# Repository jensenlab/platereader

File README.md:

<p align="center">
  <b>Instantaneous Spectrophotometer for 96 Well Plate</b><br><br>
  Adam Dama<br>
  Jensen Lab<br>
  University of Illinois at Urbana-Champaign<br>
  Department of Bioengineering and Carl R. Woese Institute for Genomic Biology<br>
  <br>
</p>

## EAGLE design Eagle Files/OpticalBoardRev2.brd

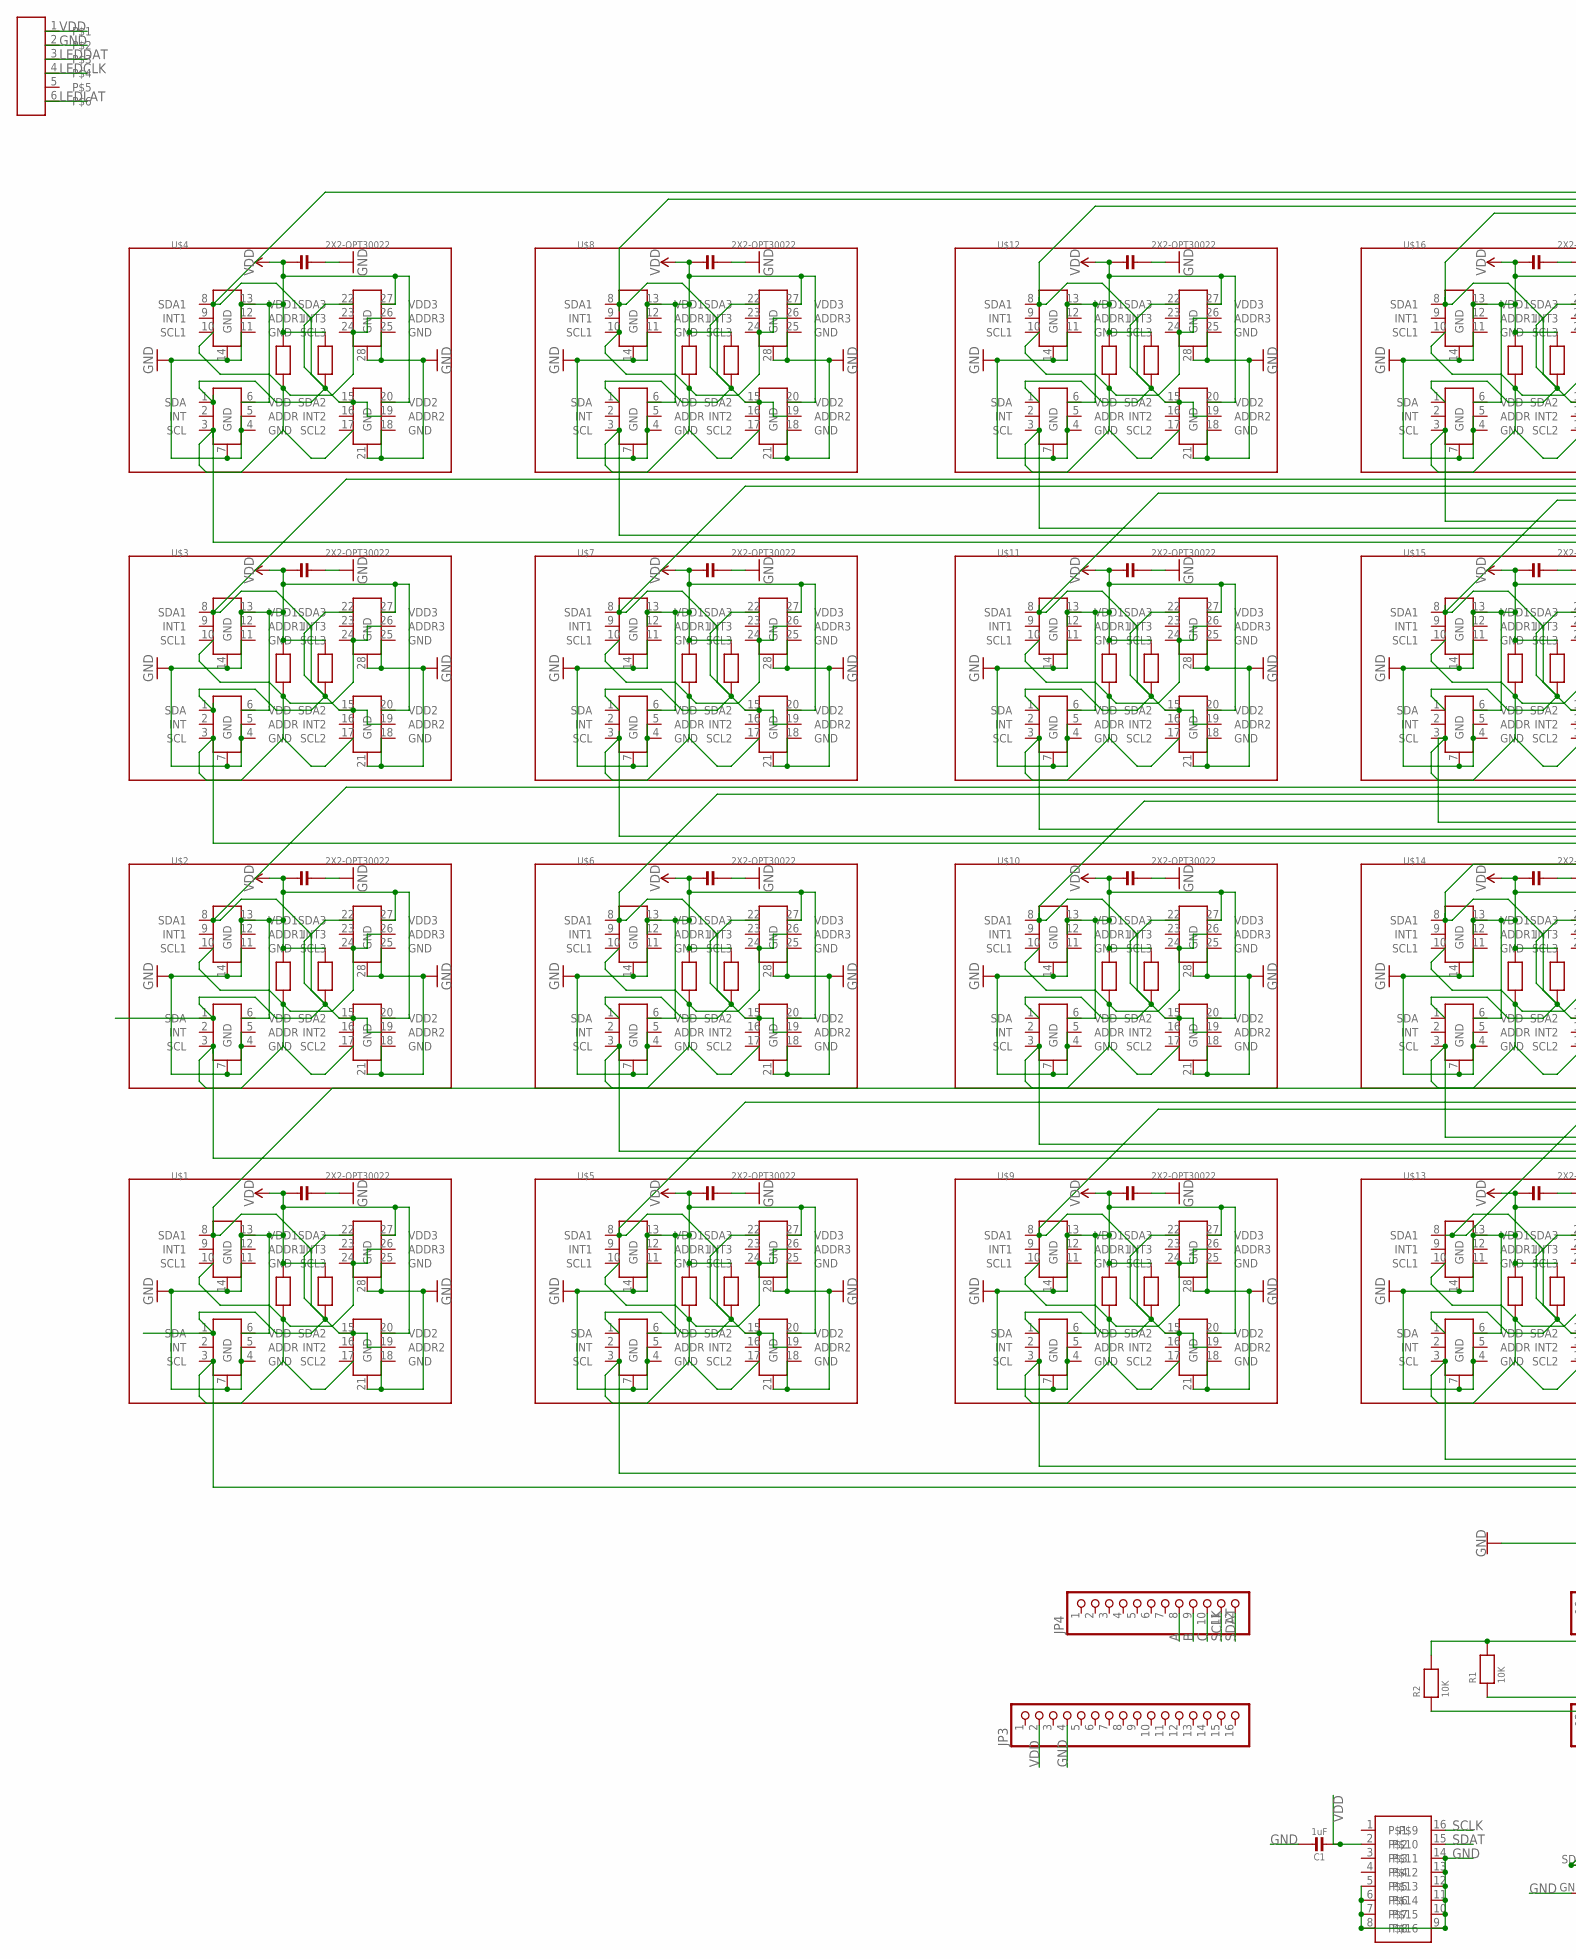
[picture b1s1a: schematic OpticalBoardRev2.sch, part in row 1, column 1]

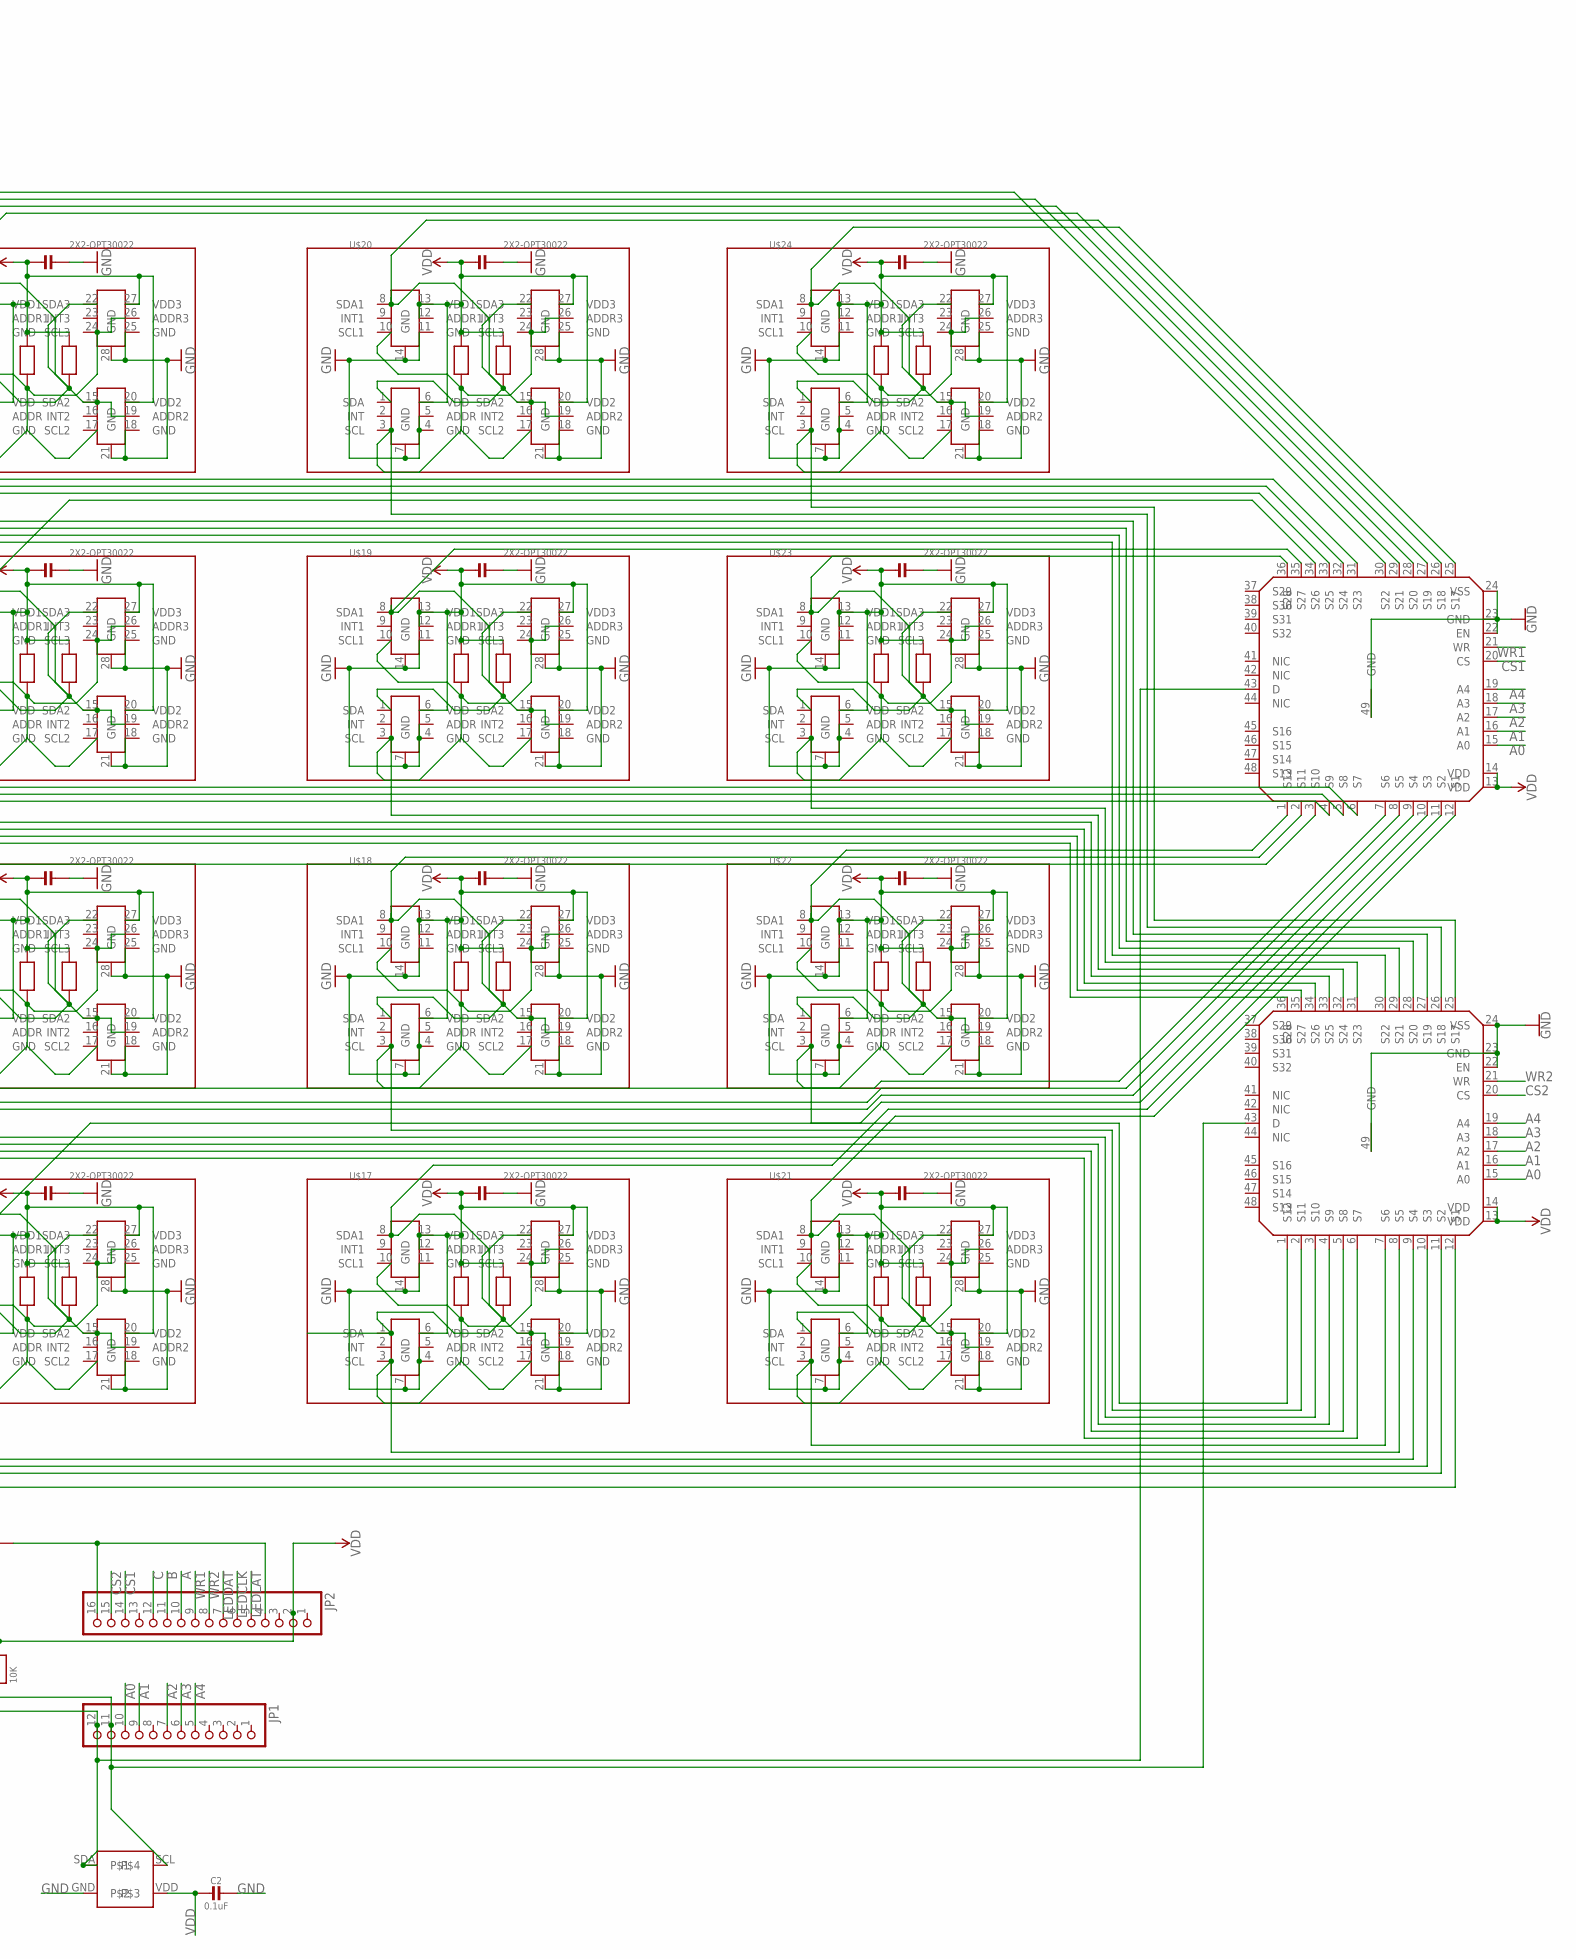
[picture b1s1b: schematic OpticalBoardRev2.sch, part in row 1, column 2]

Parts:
C1: 1uF; _0805
C2: 0.1uF; _0805
JP1, JP4: HEADER-1X12; 1X12_ROUND
JP2, JP3: HEADER-1X16ROUND; 1X16_ROUND
R1, R2: 10K; _0805
U$1, U$2, U$3, U$4, U$5, U$6, U$7, U$8, U$9, U$10, U$11, U$12, U$13, U$14, U$15, U$16, U$17, U$18, U$19, U$20, U$21, U$22, U$23, U$24: 2X2-OPT30022; 2X2-OPT3002-2
U$25: CONNECTOR_6PIN
U$26: 32MUXTOP; 32MUX
U$27: 32MUXBOT; 32MUX_BOT
U$28: RTC
U$29: TH_NEW

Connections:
A: JP2.10, JP4.8
A0: JP1.10, U$26.15 (A0), U$27.15 (A0)
A1: JP1.9, U$26.16 (A1), U$27.16 (A1)
A2: JP1.7, U$26.17 (A2), U$27.17 (A2)
A3: JP1.6, U$26.18 (A3), U$27.18 (A3)
A4: JP1.5, U$26.19 (A4), U$27.19 (A4)
B: JP2.11, JP4.9
C: JP2.12, JP4.10
CS1: JP2.14, U$26.20 (CS)
CS2: JP2.15, U$27.20 (CS)
GND: C1.1, C2.1, JP2.4, JP2.16, JP3.4, U$1.4 (GND), U$1.5 (ADDR), U$1.7 (GND), U$1.11 (GND), U$1.14 (GND), U$1.18 (GND), U$1.21 (GND), U$1.25 (GND), U$1.28 (GND), U$1.30 (GND), U$2.4 (GND), U$2.5 (ADDR), U$2.7 (GND), U$2.11 (GND), U$2.14 (GND), U$2.18 (GND), U$2.21 (GND), U$2.25 (GND), U$2.28 (GND), U$2.30 (GND), U$3.4 (GND), U$3.5 (ADDR), U$3.7 (GND), U$3.11 (GND), U$3.14 (GND), U$3.18 (GND), U$3.21 (GND), U$3.25 (GND), U$3.28 (GND), U$3.30 (GND), U$4.4 (GND), U$4.5 (ADDR), U$4.7 (GND), U$4.11 (GND), U$4.14 (GND), U$4.18 (GND), U$4.21 (GND), U$4.25 (GND), U$4.28 (GND), U$4.30 (GND), U$5.4 (GND), U$5.5 (ADDR), U$5.7 (GND), U$5.11 (GND), U$5.14 (GND), U$5.18 (GND), U$5.21 (GND), U$5.25 (GND), U$5.28 (GND), U$5.30 (GND), U$6.4 (GND), U$6.5 (ADDR), U$6.7 (GND), U$6.11 (GND), U$6.14 (GND), U$6.18 (GND), U$6.21 (GND), U$6.25 (GND), U$6.28 (GND), U$6.30 (GND), U$7.4 (GND), U$7.5 (ADDR), U$7.7 (GND), U$7.11 (GND), U$7.14 (GND), U$7.18 (GND), U$7.21 (GND), U$7.25 (GND), U$7.28 (GND), U$7.30 (GND), U$8.4 (GND), U$8.5 (ADDR), U$8.7 (GND), U$8.11 (GND), U$8.14 (GND), U$8.18 (GND), U$8.21 (GND), U$8.25 (GND), U$8.28 (GND), U$8.30 (GND), U$9.4 (GND), U$9.5 (ADDR), U$9.7 (GND), U$9.11 (GND), U$9.14 (GND), U$9.18 (GND), U$9.21 (GND), U$9.25 (GND), U$9.28 (GND), U$9.30 (GND), U$10.4 (GND), U$10.5 (ADDR), U$10.7 (GND), U$10.11 (GND), U$10.14 (GND), U$10.18 (GND), U$10.21 (GND), U$10.25 (GND), U$10.28 (GND), U$10.30 (GND), U$11.4 (GND), U$11.5 (ADDR), U$11.7 (GND), U$11.11 (GND), U$11.14 (GND), U$11.18 (GND), U$11.21 (GND), U$11.25 (GND), U$11.28 (GND), U$11.30 (GND), U$12.4 (GND), U$12.5 (ADDR), U$12.7 (GND), U$12.11 (GND), U$12.14 (GND), U$12.18 (GND), U$12.21 (GND), U$12.25 (GND), U$12.28 (GND), U$12.30 (GND), U$13.4 (GND), U$13.5 (ADDR), U$13.7 (GND), U$13.11 (GND), U$13.14 (GND), U$13.18 (GND), U$13.21 (GND), U$13.25 (GND), U$13.28 (GND), U$13.30 (GND), U$14.4 (GND), U$14.5 (ADDR), U$14.7 (GND), U$14.11 (GND), U$14.14 (GND), U$14.18 (GND), U$14.21 (GND), U$14.25 (GND), U$14.28 (GND), U$14.30 (GND), U$15.4 (GND), U$15.5 (ADDR), U$15.7 (GND), U$15.11 (GND), U$15.14 (GND), U$15.18 (GND), U$15.21 (GND), U$15.25 (GND), U$15.28 (GND), U$15.30 (GND), U$16.4 (GND), U$16.5 (ADDR), U$16.7 (GND), U$16.11 (GND), U$16.14 (GND), U$16.18 (GND), U$16.21 (GND), U$16.25 (GND), U$16.28 (GND), U$16.30 (GND), U$17.4 (GND), U$17.5 (ADDR), U$17.7 (GND), U$17.11 (GND), U$17.14 (GND), U$17.18 (GND), U$17.21 (GND), U$17.25 (GND), U$17.28 (GND), U$17.30 (GND), U$18.4 (GND), U$18.5 (ADDR), U$18.7 (GND), U$18.11 (GND), U$18.14 (GND), U$18.18 (GND), U$18.21 (GND), U$18.25 (GND), U$18.28 (GND), U$18.30 (GND), U$19.4 (GND), U$19.5 (ADDR), U$19.7 (GND), U$19.11 (GND), U$19.14 (GND), U$19.18 (GND), U$19.21 (GND), U$19.25 (GND), U$19.28 (GND), U$19.30 (GND), U$20.4 (GND), U$20.5 (ADDR), U$20.7 (GND), U$20.11 (GND), U$20.14 (GND), U$20.18 (GND), U$20.21 (GND), U$20.25 (GND), U$20.28 (GND), U$20.30 (GND), U$21.4 (GND), U$21.5 (ADDR), U$21.7 (GND), U$21.11 (GND), U$21.14 (GND), U$21.18 (GND), U$21.21 (GND), U$21.25 (GND), U$21.28 (GND), U$21.30 (GND), U$22.4 (GND), U$22.5 (ADDR), U$22.7 (GND), U$22.11 (GND), U$22.14 (GND), U$22.18 (GND), U$22.21 (GND), U$22.25 (GND), U$22.28 (GND), U$22.30 (GND), U$23.4 (GND), U$23.5 (ADDR), U$23.7 (GND), U$23.11 (GND), U$23.14 (GND), U$23.18 (GND), U$23.21 (GND), U$23.25 (GND), U$23.28 (GND), U$23.30 (GND), U$24.4 (GND), U$24.5 (ADDR), U$24.7 (GND), U$24.11 (GND), U$24.14 (GND), U$24.18 (GND), U$24.21 (GND), U$24.25 (GND), U$24.28 (GND), U$24.30 (GND), U$25.2, U$26.22 (EN), U$26.23 (GND), U$26.24 (VSS), U$26.49 (GND), U$27.22 (EN), U$27.23 (GND), U$27.24 (VSS), U$27.49 (GND), U$28.5, U$28.6, U$28.7, U$28.8, U$28.9, U$28.10, U$28.11, U$28.12, U$28.13, U$28.14, U$29.GND
LEDCLK: JP2.6, U$25.4
LEDDAT: JP2.7, U$25.3
LEDLAT: JP2.5, U$25.6
SCL1: U$1.3 (SCL), U$1.10 (SCL1), U$1.17 (SCL2), U$1.24 (SCL3), U$1.26 (ADDR3), U$1.31 (R1+), U$27.12 (S1)
SCL2: U$2.3 (SCL), U$2.10 (SCL1), U$2.17 (SCL2), U$2.24 (SCL3), U$2.26 (ADDR3), U$2.31 (R1+), U$27.6 (S7)
SCL3: U$3.3 (SCL), U$3.10 (SCL1), U$3.17 (SCL2), U$3.24 (SCL3), U$3.26 (ADDR3), U$3.31 (R1+), U$27.36 (S28)
SCL4: U$4.3 (SCL), U$4.10 (SCL1), U$4.17 (SCL2), U$4.24 (SCL3), U$4.26 (ADDR3), U$4.31 (R1+), U$27.30 (S22)
SCL5: U$5.3 (SCL), U$5.10 (SCL1), U$5.17 (SCL2), U$5.24 (SCL3), U$5.26 (ADDR3), U$5.31 (R1+), U$27.11 (S2)
SCL6: U$6.3 (SCL), U$6.10 (SCL1), U$6.17 (SCL2), U$6.24 (SCL3), U$6.26 (ADDR3), U$6.31 (R1+), U$27.5 (S8)
SCL7: U$7.3 (SCL), U$7.10 (SCL1), U$7.17 (SCL2), U$7.24 (SCL3), U$7.26 (ADDR3), U$7.31 (R1+), U$27.35 (S27)
SCL8: U$8.3 (SCL), U$8.10 (SCL1), U$8.17 (SCL2), U$8.24 (SCL3), U$8.26 (ADDR3), U$8.31 (R1+), U$27.29 (S21)
SCL9: U$9.3 (SCL), U$9.10 (SCL1), U$9.17 (SCL2), U$9.24 (SCL3), U$9.26 (ADDR3), U$9.31 (R1+), U$27.10 (S3)
SCL10: U$10.3 (SCL), U$10.10 (SCL1), U$10.17 (SCL2), U$10.24 (SCL3), U$10.26 (ADDR3), U$10.31 (R1+), U$27.4 (S9)
SCL11: U$11.3 (SCL), U$11.10 (SCL1), U$11.17 (SCL2), U$11.24 (SCL3), U$11.26 (ADDR3), U$11.31 (R1+), U$27.34 (S26)
SCL12: U$12.3 (SCL), U$12.10 (SCL1), U$12.17 (SCL2), U$12.24 (SCL3), U$12.26 (ADDR3), U$12.31 (R1+), U$27.28 (S20)
SCL13: U$13.3 (SCL), U$13.10 (SCL1), U$13.17 (SCL2), U$13.24 (SCL3), U$13.26 (ADDR3), U$13.31 (R1+), U$27.9 (S4)
SCL14: U$14.3 (SCL), U$14.10 (SCL1), U$14.17 (SCL2), U$14.24 (SCL3), U$14.26 (ADDR3), U$14.31 (R1+), U$27.3 (S10)
SCL15: U$15.3 (SCL), U$15.10 (SCL1), U$15.17 (SCL2), U$15.24 (SCL3), U$15.26 (ADDR3), U$15.31 (R1+), U$27.33 (S25)
SCL16: U$16.3 (SCL), U$16.10 (SCL1), U$16.17 (SCL2), U$16.24 (SCL3), U$16.26 (ADDR3), U$16.31 (R1+), U$27.27 (S19)
SCL17: U$17.3 (SCL), U$17.10 (SCL1), U$17.17 (SCL2), U$17.24 (SCL3), U$17.26 (ADDR3), U$17.31 (R1+), U$27.8 (S5)
SCL18: U$18.3 (SCL), U$18.10 (SCL1), U$18.17 (SCL2), U$18.24 (SCL3), U$18.26 (ADDR3), U$18.31 (R1+), U$27.2 (S11)
SCL19: U$19.3 (SCL), U$19.10 (SCL1), U$19.17 (SCL2), U$19.24 (SCL3), U$19.26 (ADDR3), U$19.31 (R1+), U$27.32 (S24)
SCL20: U$20.3 (SCL), U$20.10 (SCL1), U$20.17 (SCL2), U$20.24 (SCL3), U$20.26 (ADDR3), U$20.31 (R1+), U$27.26 (S18)
SCL21: U$21.3 (SCL), U$21.10 (SCL1), U$21.17 (SCL2), U$21.24 (SCL3), U$21.26 (ADDR3), U$21.31 (R1+), U$27.7 (S6)
SCL22: U$22.3 (SCL), U$22.10 (SCL1), U$22.17 (SCL2), U$22.24 (SCL3), U$22.26 (ADDR3), U$22.31 (R1+), U$27.1 (S12)
SCL23: U$23.3 (SCL), U$23.10 (SCL1), U$23.17 (SCL2), U$23.24 (SCL3), U$23.26 (ADDR3), U$23.31 (R1+), U$27.31 (S23)
SCL24: U$24.3 (SCL), U$24.10 (SCL1), U$24.17 (SCL2), U$24.24 (SCL3), U$24.26 (ADDR3), U$24.31 (R1+), U$27.25 (S17)
SCLK: JP1.11, JP4.11, R1.1, U$27.43 (D), U$28.16, U$29.SCL
SDA1: U$1.1 (SDA), U$1.8 (SDA1), U$1.15 (SDA2), U$1.19 (ADDR2), U$1.22 (SDA3), U$1.33 (R2+), U$26.7 (S6)
SDA2: U$2.1 (SDA), U$2.8 (SDA1), U$2.15 (SDA2), U$2.19 (ADDR2), U$2.22 (SDA3), U$2.33 (R2+), U$26.6 (S7)
SDA3: U$3.1 (SDA), U$3.8 (SDA1), U$3.15 (SDA2), U$3.19 (ADDR2), U$3.22 (SDA3), U$3.33 (R2+), U$26.31 (S23)
SDA4: U$4.1 (SDA), U$4.8 (SDA1), U$4.15 (SDA2), U$4.19 (ADDR2), U$4.22 (SDA3), U$4.33 (R2+), U$26.30 (S22)
SDA5: U$5.1 (SDA), U$5.8 (SDA1), U$5.15 (SDA2), U$5.19 (ADDR2), U$5.22 (SDA3), U$5.33 (R2+), U$26.8 (S5)
SDA6: U$6.1 (SDA), U$6.8 (SDA1), U$6.15 (SDA2), U$6.19 (ADDR2), U$6.22 (SDA3), U$6.33 (R2+), U$26.5 (S8)
SDA7: U$7.1 (SDA), U$7.8 (SDA1), U$7.15 (SDA2), U$7.19 (ADDR2), U$7.22 (SDA3), U$7.33 (R2+), U$26.32 (S24)
SDA8: U$8.1 (SDA), U$8.8 (SDA1), U$8.15 (SDA2), U$8.19 (ADDR2), U$8.22 (SDA3), U$8.33 (R2+), U$26.29 (S21)
SDA9: U$9.1 (SDA), U$9.8 (SDA1), U$9.15 (SDA2), U$9.19 (ADDR2), U$9.22 (SDA3), U$9.33 (R2+), U$26.9 (S4)
SDA10: U$10.1 (SDA), U$10.8 (SDA1), U$10.15 (SDA2), U$10.19 (ADDR2), U$10.22 (SDA3), U$10.33 (R2+), U$26.4 (S9)
SDA11: U$11.1 (SDA), U$11.8 (SDA1), U$11.15 (SDA2), U$11.19 (ADDR2), U$11.22 (SDA3), U$11.33 (R2+), U$26.33 (S25)
SDA12: U$12.1 (SDA), U$12.8 (SDA1), U$12.15 (SDA2), U$12.19 (ADDR2), U$12.22 (SDA3), U$12.33 (R2+), U$26.28 (S20)
SDA13: U$13.1 (SDA), U$13.8 (SDA1), U$13.15 (SDA2), U$13.19 (ADDR2), U$13.22 (SDA3), U$13.33 (R2+), U$26.10 (S3)
SDA14: U$14.1 (SDA), U$14.8 (SDA1), U$14.15 (SDA2), U$14.19 (ADDR2), U$14.22 (SDA3), U$14.33 (R2+), U$26.3 (S10)
SDA15: U$15.1 (SDA), U$15.8 (SDA1), U$15.15 (SDA2), U$15.19 (ADDR2), U$15.22 (SDA3), U$15.33 (R2+), U$26.34 (S26)
SDA16: U$16.1 (SDA), U$16.8 (SDA1), U$16.15 (SDA2), U$16.19 (ADDR2), U$16.22 (SDA3), U$16.33 (R2+), U$26.27 (S19)
SDA17: U$17.1 (SDA), U$17.8 (SDA1), U$17.15 (SDA2), U$17.19 (ADDR2), U$17.22 (SDA3), U$17.33 (R2+), U$26.11 (S2)
SDA18: U$18.1 (SDA), U$18.8 (SDA1), U$18.15 (SDA2), U$18.19 (ADDR2), U$18.22 (SDA3), U$18.33 (R2+), U$26.2 (S11)
SDA19: U$19.1 (SDA), U$19.8 (SDA1), U$19.15 (SDA2), U$19.19 (ADDR2), U$19.22 (SDA3), U$19.33 (R2+), U$26.35 (S27)
SDA20: U$20.1 (SDA), U$20.8 (SDA1), U$20.15 (SDA2), U$20.19 (ADDR2), U$20.22 (SDA3), U$20.33 (R2+), U$26.26 (S18)
SDA21: U$21.1 (SDA), U$21.8 (SDA1), U$21.15 (SDA2), U$21.19 (ADDR2), U$21.22 (SDA3), U$21.33 (R2+), U$26.12 (S1)
SDA22: U$22.1 (SDA), U$22.8 (SDA1), U$22.15 (SDA2), U$22.19 (ADDR2), U$22.22 (SDA3), U$22.33 (R2+), U$26.1 (S12)
SDA23: U$23.1 (SDA), U$23.8 (SDA1), U$23.15 (SDA2), U$23.19 (ADDR2), U$23.22 (SDA3), U$23.33 (R2+), U$26.36 (S28)
SDA24: U$24.1 (SDA), U$24.8 (SDA1), U$24.15 (SDA2), U$24.19 (ADDR2), U$24.22 (SDA3), U$24.33 (R2+), U$26.25 (S17)
SDAT: JP1.12, JP4.12, R2.1, U$26.43 (D), U$28.15, U$29.SDA
VDD: C1.2, C2.2, JP2.2, JP3.2, R1.2, R2.2, U$1.6 (VDD), U$1.12 (ADDR1), U$1.13 (VDD1), U$1.20 (VDD2), U$1.27 (VDD3), U$1.29 (C+), U$1.32 (GND), U$1.34 (GND), U$2.6 (VDD), U$2.12 (ADDR1), U$2.13 (VDD1), U$2.20 (VDD2), U$2.27 (VDD3), U$2.29 (C+), U$2.32 (GND), U$2.34 (GND), U$3.6 (VDD), U$3.12 (ADDR1), U$3.13 (VDD1), U$3.20 (VDD2), U$3.27 (VDD3), U$3.29 (C+), U$3.32 (GND), U$3.34 (GND), U$4.6 (VDD), U$4.12 (ADDR1), U$4.13 (VDD1), U$4.20 (VDD2), U$4.27 (VDD3), U$4.29 (C+), U$4.32 (GND), U$4.34 (GND), U$5.6 (VDD), U$5.12 (ADDR1), U$5.13 (VDD1), U$5.20 (VDD2), U$5.27 (VDD3), U$5.29 (C+), U$5.32 (GND), U$5.34 (GND), U$6.6 (VDD), U$6.12 (ADDR1), U$6.13 (VDD1), U$6.20 (VDD2), U$6.27 (VDD3), U$6.29 (C+), U$6.32 (GND), U$6.34 (GND), U$7.6 (VDD), U$7.12 (ADDR1), U$7.13 (VDD1), U$7.20 (VDD2), U$7.27 (VDD3), U$7.29 (C+), U$7.32 (GND), U$7.34 (GND), U$8.6 (VDD), U$8.12 (ADDR1), U$8.13 (VDD1), U$8.20 (VDD2), U$8.27 (VDD3), U$8.29 (C+), U$8.32 (GND), U$8.34 (GND), U$9.6 (VDD), U$9.12 (ADDR1), U$9.13 (VDD1), U$9.20 (VDD2), U$9.27 (VDD3), U$9.29 (C+), U$9.32 (GND), U$9.34 (GND), U$10.6 (VDD), U$10.12 (ADDR1), U$10.13 (VDD1), U$10.20 (VDD2), U$10.27 (VDD3), U$10.29 (C+), U$10.32 (GND), U$10.34 (GND), U$11.6 (VDD), U$11.12 (ADDR1), U$11.13 (VDD1), U$11.20 (VDD2), U$11.27 (VDD3), U$11.29 (C+), U$11.32 (GND), U$11.34 (GND), U$12.6 (VDD), U$12.12 (ADDR1), U$12.13 (VDD1), U$12.20 (VDD2), U$12.27 (VDD3), U$12.29 (C+), U$12.32 (GND), U$12.34 (GND), U$13.6 (VDD), U$13.12 (ADDR1), U$13.13 (VDD1), U$13.20 (VDD2), U$13.27 (VDD3), U$13.29 (C+), U$13.32 (GND), U$13.34 (GND), U$14.6 (VDD), U$14.12 (ADDR1), U$14.13 (VDD1), U$14.20 (VDD2), U$14.27 (VDD3), U$14.29 (C+), U$14.32 (GND), U$14.34 (GND), U$15.6 (VDD), U$15.12 (ADDR1), U$15.13 (VDD1), U$15.20 (VDD2), U$15.27 (VDD3), U$15.29 (C+), U$15.32 (GND), U$15.34 (GND), U$16.6 (VDD), U$16.12 (ADDR1), U$16.13 (VDD1), U$16.20 (VDD2), U$16.27 (VDD3), U$16.29 (C+), U$16.32 (GND), U$16.34 (GND), U$17.6 (VDD), U$17.12 (ADDR1), U$17.13 (VDD1), U$17.20 (VDD2), U$17.27 (VDD3), U$17.29 (C+), U$17.32 (GND), U$17.34 (GND), U$18.6 (VDD), U$18.12 (ADDR1), U$18.13 (VDD1), U$18.20 (VDD2), U$18.27 (VDD3), U$18.29 (C+), U$18.32 (GND), U$18.34 (GND), U$19.6 (VDD), U$19.12 (ADDR1), U$19.13 (VDD1), U$19.20 (VDD2), U$19.27 (VDD3), U$19.29 (C+), U$19.32 (GND), U$19.34 (GND), U$20.6 (VDD), U$20.12 (ADDR1), U$20.13 (VDD1), U$20.20 (VDD2), U$20.27 (VDD3), U$20.29 (C+), U$20.32 (GND), U$20.34 (GND), U$21.6 (VDD), U$21.12 (ADDR1), U$21.13 (VDD1), U$21.20 (VDD2), U$21.27 (VDD3), U$21.29 (C+), U$21.32 (GND), U$21.34 (GND), U$22.6 (VDD), U$22.12 (ADDR1), U$22.13 (VDD1), U$22.20 (VDD2), U$22.27 (VDD3), U$22.29 (C+), U$22.32 (GND), U$22.34 (GND), U$23.6 (VDD), U$23.12 (ADDR1), U$23.13 (VDD1), U$23.20 (VDD2), U$23.27 (VDD3), U$23.29 (C+), U$23.32 (GND), U$23.34 (GND), U$24.6 (VDD), U$24.12 (ADDR1), U$24.13 (VDD1), U$24.20 (VDD2), U$24.27 (VDD3), U$24.29 (C+), U$24.32 (GND), U$24.34 (GND), U$25.1, U$26.13 (VDD), U$26.14 (VDD), U$27.13 (VDD), U$27.14 (VDD), U$28.2, U$29.VDD
WR1: JP2.9, U$26.21 (WR)
WR2: JP2.8, U$27.21 (WR)

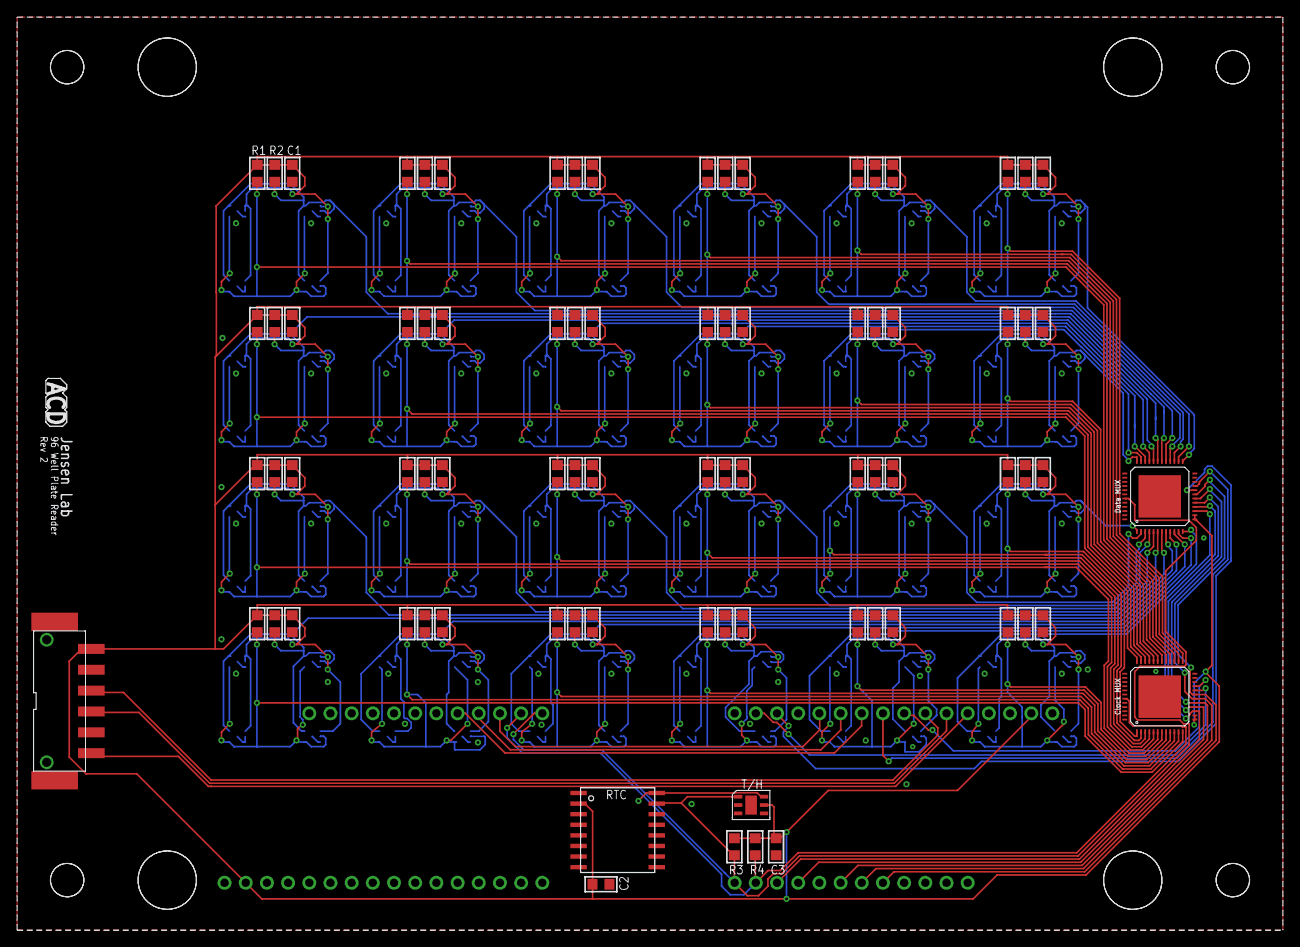
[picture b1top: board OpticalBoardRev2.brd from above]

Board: 2 copper layers, 151.8 x 109.5 mm, 37 parts (1 on the bottom side), 67 nets.

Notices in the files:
parts and their libraries:
SparkFun-PowerSymbols: Licensing: Creative Commons ShareAlike 4.0 International - https://creativecommons.org/licenses/by-sa/4.0
